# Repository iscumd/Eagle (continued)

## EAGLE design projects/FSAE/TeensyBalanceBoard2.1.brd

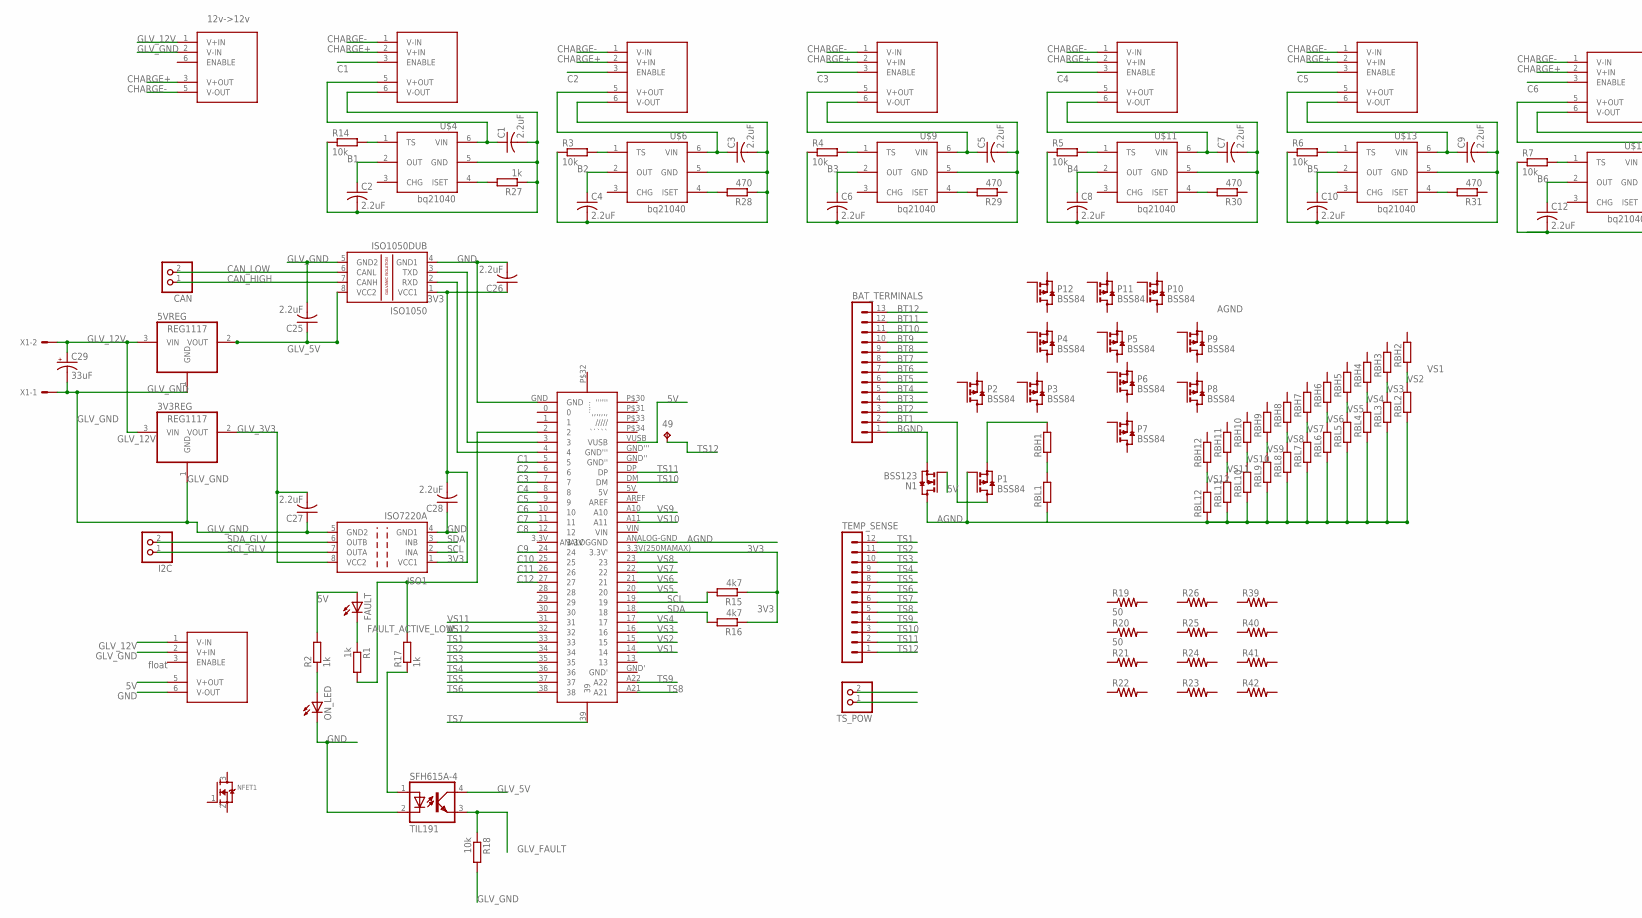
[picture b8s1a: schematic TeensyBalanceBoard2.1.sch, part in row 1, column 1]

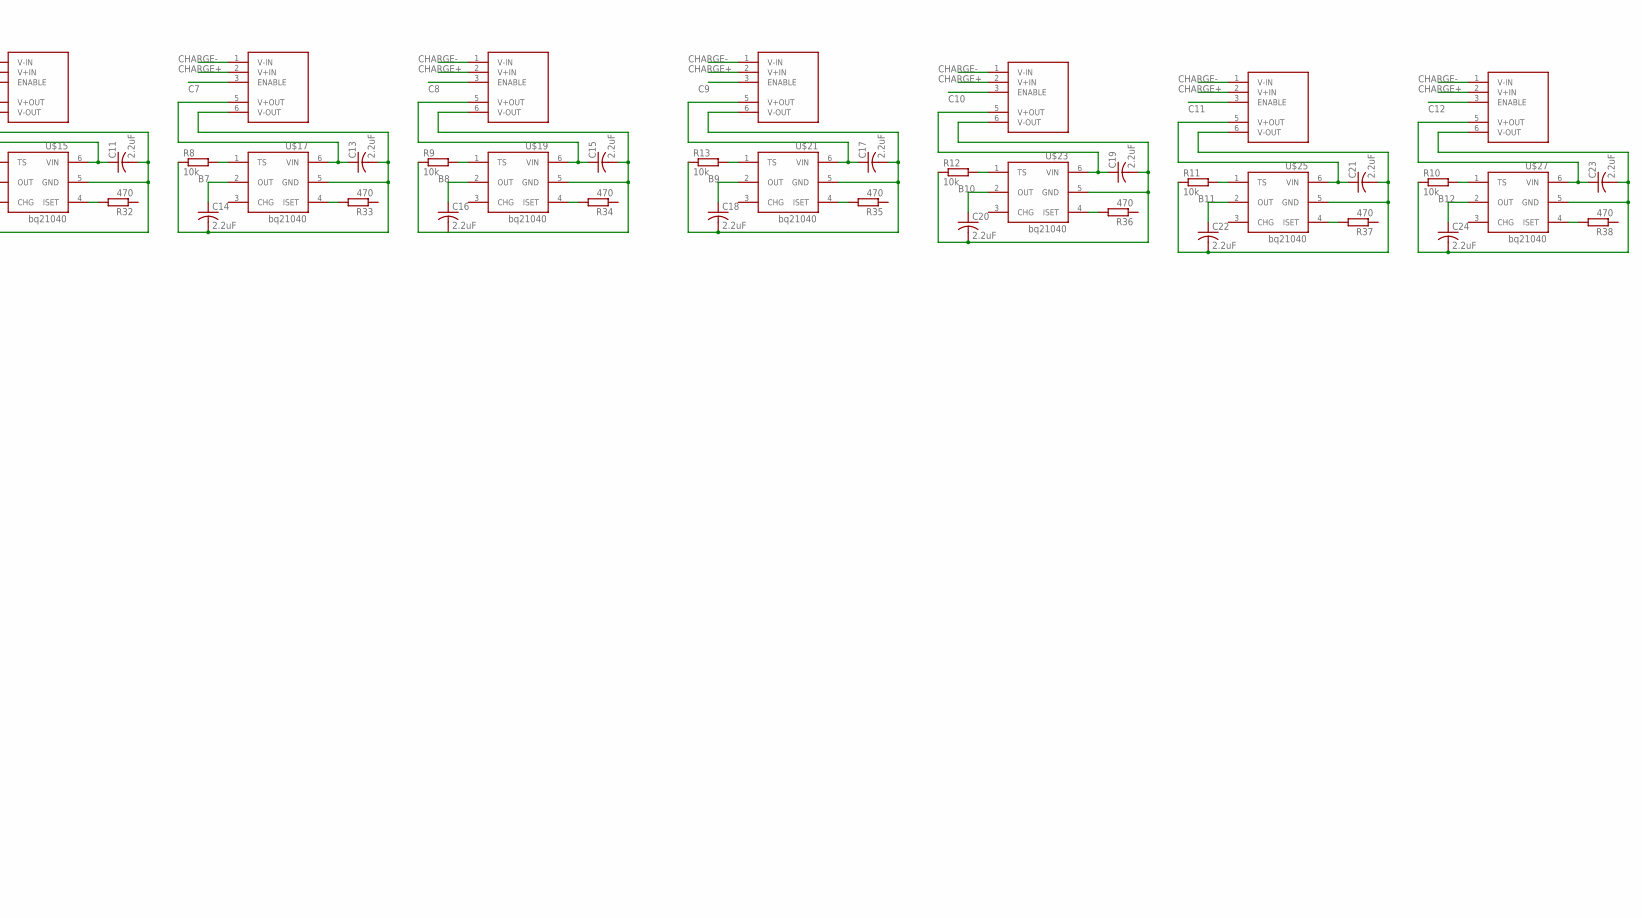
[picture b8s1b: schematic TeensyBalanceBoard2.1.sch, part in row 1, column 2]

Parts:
3V3REG, 5VREG: REG1117; SOT223
49: TPTP20SQ; TP20SQ
BAT_TERMINALS: MA13-1
C1, C2, C3, C4, C5, C6, C7, C8, C9, C10, C11, C12, C13, C14, C15, C16, C17, C18, C19, C20, C21, C22, C23, C24, C25, C26, C27, C28: 2.2uF; C0603
C29: 33uF; E3,5-10
CAN: PINHD-1X2; 1X02
FAULT: LEDSMT1206; 1206
I2C: PINHD-1X2; 1X02
ISO1: ISO7220A; SO-08
ISO1050: ISO1050DUB; DUB-R-PDSO-G8
N1: BSS123; SOT23
NFET1: MOSFET-NREFLOW; SOT23
ON_LED: LEDSMT1206; 1206
P1, P2, P3, P4, P5, P6, P7, P8, P9, P10, P11, P12: BSS84; SOT23
R1, R2, R17, R27: 1k; R0603
R3, R4, R5, R6, R7, R8, R9, R10, R11, R12, R13, R14, R18: 10k; R0603
R15, R16: 4k7; R0603
R19, R20: 50; R1206W
R21, R22, R23, R24, R25, R26, R39, R40, R41, R42: R-US_R1206W; R1206W
R28, R29, R30, R31, R32, R33, R34, R35, R36, R37, R38: 470; R0603
RBH1, RBH2, RBH3, RBH4, RBH5, RBH6, RBH7, RBH8, RBH9, RBH10, RBH11, RBH12: RR0603; R0603
RBL1, RBL2, RBL3, RBL4, RBL5, RBL6, RBL7, RBL8, RBL9, RBL10, RBL11, RBL12: RR0603; R0603
SFH615A-4: TIL191; DIL04
TEMP_SENSE: MA12-1
TS_POW: PINHD-1X2; 1X02
U$1: TEENSY3.6
U$2, U$3, U$5, U$7, U$10, U$12, U$14, U$16, U$18, U$20, U$22, U$24, U$26: EC4SAW-24S05N6-2411WI; EC4SAW-24S05N
U$4, U$6, U$9, U$11, U$13, U$15, U$17, U$19, U$21, U$23, U$25, U$27: 10F200T; SOT23-6
U$8: PDQ30-Q24-S12-D
X1: KK-156-2

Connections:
3V3: C26.1, C28.2, ISO1.1 (VCC1), ISO1050.1 (VCC1), R15.1, R16.1, TS_POW.2, U$1.3.3V(250MAMAX) (3.3V')
5V: FAULT.A, N1.1 (G), R2.2, U$1.VUSB, U$3.5 (V+OUT)
AGND: C1.2, C2.2, N1.3 (D), P1.1 (G), R14.1, R27.1, RBL1.1, RBL2.1, RBL3.1, RBL4.1, RBL5.1, RBL6.1, RBL7.1, RBL8.1, RBL9.1, RBL10.1, RBL11.1, RBL12.1, TS_POW.1, U$1.ANALOG-GND (ANALOGGND), U$2.6 (V-OUT), U$4.5 (GND)
B1: C2.1, C3.2, C4.2, R3.1, R28.1, U$4.2 (OUT), U$5.6 (V-OUT), U$6.5 (GND)
B2: C4.1, C5.2, C6.2, R4.1, U$6.2 (OUT), U$7.6 (V-OUT), U$9.5 (GND)
B3: C6.1, C7.2, C8.2, R5.1, U$9.2 (OUT), U$10.6 (V-OUT), U$11.5 (GND)
B4: C8.1, C9.2, C10.2, R6.1, U$11.2 (OUT), U$12.6 (V-OUT), U$13.5 (GND)
B5: C10.1, C11.2, C12.2, R7.1, U$13.2 (OUT), U$14.6 (V-OUT), U$15.5 (GND)
B6: C12.1, C13.2, C14.2, R8.1, U$15.2 (OUT), U$16.6 (V-OUT), U$17.5 (GND)
B7: C14.1, C15.2, C16.2, R9.1, U$17.2 (OUT), U$18.6 (V-OUT), U$19.5 (GND)
B8: C16.1, C17.2, C18.2, R13.1, U$19.2 (OUT), U$20.6 (V-OUT), U$21.5 (GND)
B9: C18.1, C19.2, C20.2, R12.1, U$21.2 (OUT), U$22.6 (V-OUT), U$23.5 (GND)
B10: C20.1, C21.2, C22.2, R11.1, U$23.2 (OUT), U$24.6 (V-OUT), U$25.5 (GND)
B11: C22.1, C23.2, C24.2, R10.1, U$25.2 (OUT), U$26.6 (V-OUT), U$27.5 (GND)
B12: C24.1, U$27.2 (OUT)
BGND: BAT_TERMINALS.1, N1.2 (S)
BT1: BAT_TERMINALS.2, P1.3 (D)
BT2: BAT_TERMINALS.3
BT3: BAT_TERMINALS.4
BT4: BAT_TERMINALS.5
BT5: BAT_TERMINALS.6
BT6: BAT_TERMINALS.7
BT7: BAT_TERMINALS.8
BT8: BAT_TERMINALS.9
BT9: BAT_TERMINALS.10
BT10: BAT_TERMINALS.11
BT11: BAT_TERMINALS.12
BT12: BAT_TERMINALS.13
C1: U$1.5, U$2.3 (ENABLE)
C2: U$1.6, U$5.3 (ENABLE)
C3: U$1.7, U$7.3 (ENABLE)
C4: U$1.8, U$10.3 (ENABLE)
C5: U$1.9, U$12.3 (ENABLE)
C6: U$1.10, U$14.3 (ENABLE)
C7: U$1.11, U$16.3 (ENABLE)
C8: U$1.12, U$18.3 (ENABLE)
C9: U$1.24, U$20.3 (ENABLE)
C10: U$1.25, U$22.3 (ENABLE)
C11: U$1.26, U$24.3 (ENABLE)
C12: U$1.27, U$26.3 (ENABLE)
CAN_HIGH: CAN.1, ISO1050.7 (CANH)
CAN_LOW: CAN.2, ISO1050.6 (CANL)
CHARGE+: U$2.2 (V+IN), U$5.2 (V+IN), U$7.2 (V+IN), U$8.3 (V+OUT), U$10.2 (V+IN), U$12.2 (V+IN), U$14.2 (V+IN), U$16.2 (V+IN), U$18.2 (V+IN), U$20.2 (V+IN), U$22.2 (V+IN), U$24.2 (V+IN), U$26.2 (V+IN)
CHARGE-: U$2.1 (V-IN), U$5.1 (V-IN), U$7.1 (V-IN), U$8.5 (V-OUT), U$10.1 (V-IN), U$12.1 (V-IN), U$14.1 (V-IN), U$16.1 (V-IN), U$18.1 (V-IN), U$20.1 (V-IN), U$22.1 (V-IN), U$24.1 (V-IN), U$26.1 (V-IN)
FAULT_ACTIVE_LOW: R1.2, R17.2, U$1.2
GLV_3V3: C27.2, ISO1.8 (VCC2)
GLV_5V: 5VREG.2 (VOUT), C25.1, ISO1050.8 (VCC2), SFH615A-4.4 (COL)
GLV_12V: 3V3REG.3 (VIN), 5VREG.3 (VIN), C29.+, U$3.1 (V-IN), U$8.1 (V+IN), X1.2
GLV_FAULT: R18.1, SFH615A-4.3 (EMIT)
GLV_GND: 3V3REG.1 (GND), 5VREG.1 (GND), C25.2, C27.1, C29.-, ISO1050.5 (GND2), U$3.2 (V+IN), U$8.2 (V-IN), X1.1
GND: C26.2, C28.1, ISO1050.4 (GND1), ON_LED.C, SFH615A-4.2 (C), U$1.GND, U$3.6 (V-OUT)
GND1: ISO1.4 (GND1)
GND2: ISO1.5 (GND2)
unnamed: C1.1, U$2.5 (V+OUT), U$4.6 (VIN)
unnamed: R17.1, SFH615A-4.1 (A)
unnamed: ISO1050.3 (TXD), U$1.3
unnamed: ISO1050.2 (RXD), U$1.4
unnamed: C3.1, U$5.5 (V+OUT), U$6.6 (VIN)
unnamed: ON_LED.A, R2.1
unnamed: FAULT.C, R1.1
unnamed: R27.2, U$4.4 (ISET)
unnamed: R28.2, U$6.4 (ISET)
unnamed: C5.1, U$7.5 (V+OUT), U$9.6 (VIN)
unnamed: R29.2, U$9.4 (ISET)
unnamed: C7.1, U$10.5 (V+OUT), U$11.6 (VIN)
unnamed: R30.2, U$11.4 (ISET)
unnamed: C9.1, U$12.5 (V+OUT), U$13.6 (VIN)
unnamed: R31.2, U$13.4 (ISET)
unnamed: C11.1, U$14.5 (V+OUT), U$15.6 (VIN)
unnamed: R32.2, U$15.4 (ISET)
unnamed: C13.1, U$16.5 (V+OUT), U$17.6 (VIN)
unnamed: R33.2, U$17.4 (ISET)
unnamed: C15.1, U$18.5 (V+OUT), U$19.6 (VIN)
unnamed: R34.2, U$19.4 (ISET)
unnamed: C17.1, U$20.5 (V+OUT), U$21.6 (VIN)
unnamed: R35.2, U$21.4 (ISET)
unnamed: C19.1, U$22.5 (V+OUT), U$23.6 (VIN)
unnamed: R36.2, U$23.4 (ISET)
unnamed: C21.1, U$24.5 (V+OUT), U$25.6 (VIN)
unnamed: R37.2, U$25.4 (ISET)
unnamed: C23.1, U$26.5 (V+OUT), U$27.6 (VIN)
unnamed: R38.2, U$27.4 (ISET)
unnamed: R3.2, U$6.1 (TS)
unnamed: R13.2, U$21.1 (TS)
unnamed: R12.2, U$23.1 (TS)
unnamed: R11.2, U$25.1 (TS)
unnamed: R10.2, U$27.1 (TS)
unnamed: R9.2, U$19.1 (TS)
unnamed: R8.2, U$17.1 (TS)
unnamed: R7.2, U$15.1 (TS)
unnamed: R6.2, U$13.1 (TS)
unnamed: R5.2, U$11.1 (TS)
unnamed: R4.2, U$9.1 (TS)
unnamed: R14.2, U$4.1 (TS)
unnamed: P1.2 (S), RBH1.2
SCL: ISO1.2 (INA), R15.2, U$1.19
SCL_GLV: I2C.1, ISO1.7 (OUTA)
SDA: ISO1.3 (INB), R16.2, U$1.18
SDA_GLV: I2C.2, ISO1.6 (OUTB)
TS1: TEMP_SENSE.12, U$1.33
TS2: TEMP_SENSE.11, U$1.34
TS3: TEMP_SENSE.10, U$1.35
TS4: TEMP_SENSE.9, U$1.36
TS5: TEMP_SENSE.8, U$1.37
TS6: TEMP_SENSE.7, U$1.38
TS7: TEMP_SENSE.6, U$1.39
TS8: TEMP_SENSE.5, U$1.A21
TS9: TEMP_SENSE.4, U$1.A22
TS10: TEMP_SENSE.3, U$1.DM
TS11: TEMP_SENSE.2, U$1.DP
TS12: 49.TP, TEMP_SENSE.1
VS1: RBH1.1, RBL1.2, U$1.14
VS2: RBH2.1, RBL2.2, U$1.15
VS3: RBH3.1, RBL3.2, U$1.16
VS4: RBH4.1, RBL4.2, U$1.17
VS5: RBH5.1, RBL5.2, U$1.20
VS6: RBH6.1, RBL6.2, U$1.21
VS7: RBH7.1, RBL7.2, U$1.22
VS8: RBH8.1, RBL8.2, U$1.23
VS9: RBH9.1, RBL9.2, U$1.A10
VS10: RBH10.1, RBL10.2, U$1.A11
VS11: RBH11.1, RBL11.2, U$1.31
VS12: RBH12.1, RBL12.2, U$1.32

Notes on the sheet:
float
12v->12v

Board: 2 copper layers, 150 parts (14 on the bottom side), 110 nets, no tracks yet.

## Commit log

2017-06-01 added Cris's Projects
2017-06-02 added BOM excel
2017-07-31 added 18650 holder
2017-08-01 updated CAPFET board to use larger caps
2017-08-08 added new motor driver project
2017-08-29 added hall effect test board
2017-09-10 made traces wider for Aaron to CNC
2017-09-17 added AC motor controller project
2017-09-18 minor updates to resistor sizes
2018-11-08 backup
